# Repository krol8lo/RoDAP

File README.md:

# RoDAP
RoDAP - Robot Dzielnie Atakujący Przeciwników. Przykładowy projekt robota minisumo

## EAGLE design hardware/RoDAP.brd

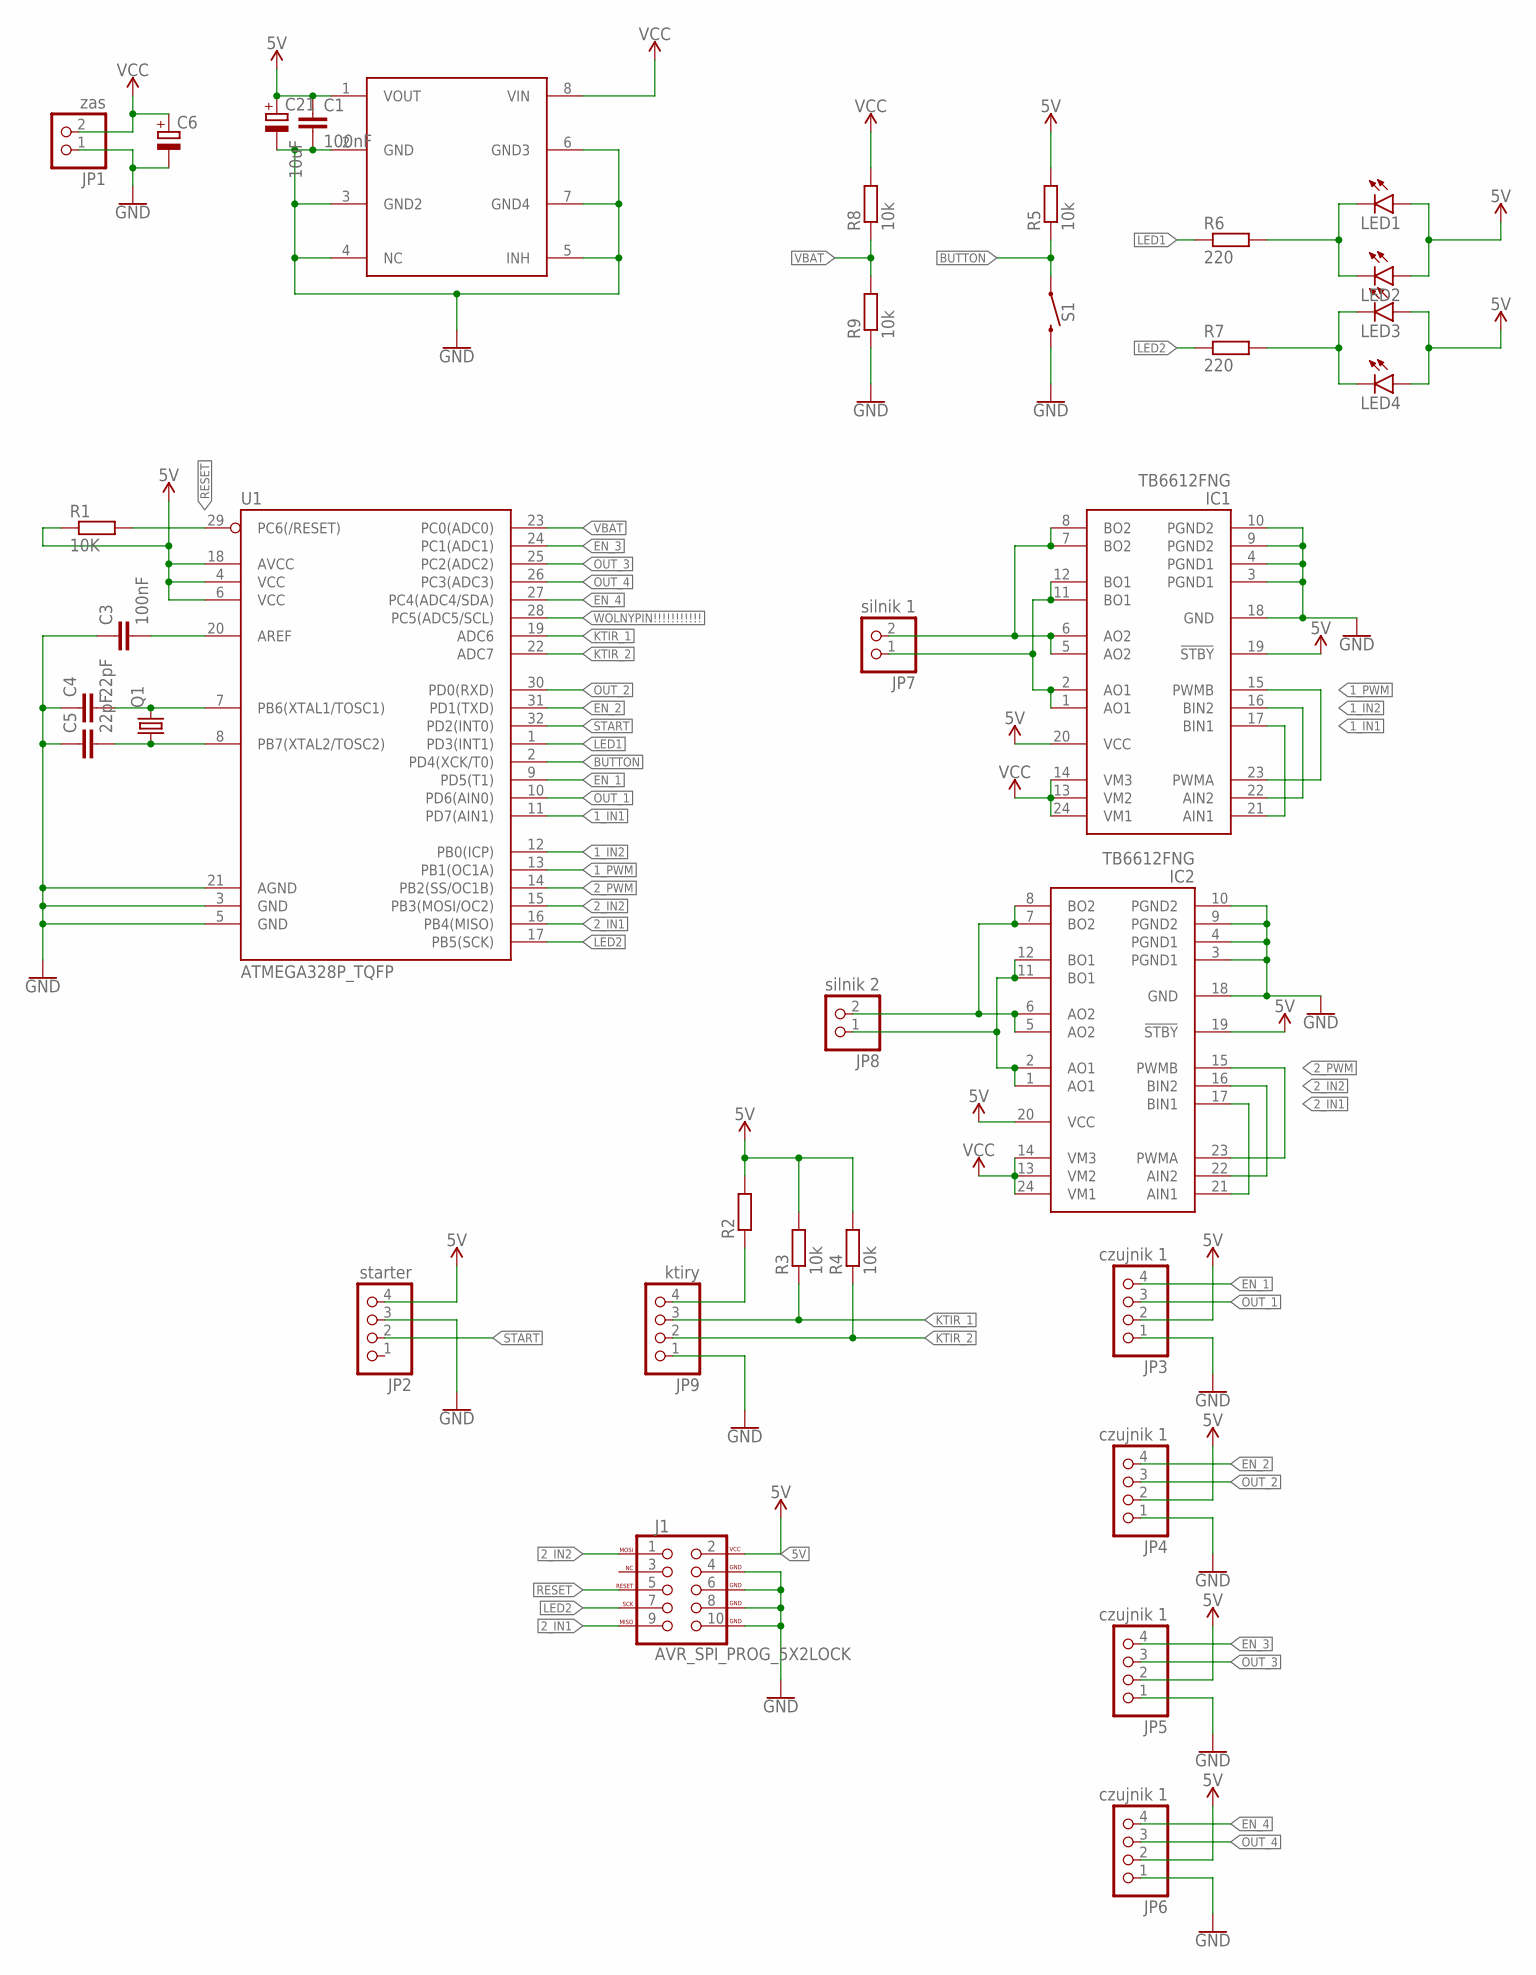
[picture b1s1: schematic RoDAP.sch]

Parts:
C1, C3: 100nF; C0805
C4, C5: 22pF; C0805
C6: CPOL-EUE2.5-7; E2,5-7
C21: 10uF; SMC_B
IC1, IC2: TB6612FNG; SSOP24
J1: AVR_SPI_PROG_5X2LOCK; 2X5-SHROUDED_LOCK
JP1: zas; 1X02
JP2: starter; 1X04
JP3, JP4, JP5, JP6: czujnik 1; 1X04
JP7: silnik 1; 1X02
JP8: silnik 2; 1X02
JP9: ktiry; 1X04
LED1, LED3: LED5MM
LED2, LED4: LEDSML0805; SML0805
Q1: CRYSTALHC49S; HC49/S
R1: 10K; R0805
R2: R-EU_R0805; R0805
R3, R4, R5, R8, R9: 10k; R0805
R6, R7: 220; R0805
S1: MOMENTARY-SWITCH-SPST-SMD-6.0X3.5MM; TACTILE_SWITCH_SMD_6.0X3.5MM
U1: ATMEGA328P_TQFP; TQFP32-08
U$4: KF50BD-TR; SOIC8-1.27-5X4MM

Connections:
1_IN1: IC1.17 (BIN1), IC1.21 (AIN1), U1.11 (PD7(AIN1))
1_IN2: IC1.16 (BIN2), IC1.22 (AIN2), U1.12 (PB0(ICP))
1_PWM: IC1.15 (PWMB), IC1.23 (PWMA), U1.13 (PB1(OC1A))
2_IN1: IC2.17 (BIN1), IC2.21 (AIN1), J1.9 (MISO), U1.16 (PB4(MISO))
2_IN2: IC2.16 (BIN2), IC2.22 (AIN2), J1.1 (MOSI), U1.15 (PB3(MOSI/OC2))
2_PWM: IC2.15 (PWMB), IC2.23 (PWMA), U1.14 (PB2(SS/OC1B))
5V: C1.1, C21.+, IC1.19 (!STBY), IC1.20 (VCC), IC2.19 (!STBY), IC2.20 (VCC), J1.2 (VCC), JP2.4, JP3.2, JP4.2, JP5.2, JP6.2, LED1.A, LED2.A, LED3.A, LED4.A, R1.1, R2.2, R3.2, R4.2, R5.2, U1.4 (VCC), U1.6 (VCC), U1.18 (AVCC), U$4.1 (VOUT)
BUTTON: R5.1, S1.1, U1.2 (PD4(XCK/T0))
EN_1: JP3.4, U1.9 (PD5(T1))
EN_2: JP4.4, U1.31 (PD1(TXD))
EN_3: JP5.4, U1.24 (PC1(ADC1))
EN_4: JP6.4, U1.27 (PC4(ADC4/SDA))
GND: C1.2, C3.1, C4.1, C5.1, C6.-, C21.-, IC1.3 (PGND1), IC1.4 (PGND1), IC1.9 (PGND2), IC1.10 (PGND2), IC1.18 (GND), IC2.3 (PGND1), IC2.4 (PGND1), IC2.9 (PGND2), IC2.10 (PGND2), IC2.18 (GND), J1.4 (GND), J1.6 (GND), J1.8 (GND), J1.10 (GND), JP1.1, JP2.3, JP3.1, JP4.1, JP5.1, JP6.1, JP9.1, R9.1, S1.2, U1.3 (GND), U1.5 (GND), U1.21 (AGND), U$4.2 (GND), U$4.3 (GND2), U$4.4 (NC), U$4.5 (INH), U$4.6 (GND3), U$4.7 (GND4)
KTIR_1: JP9.3, R3.1, U1.19 (ADC6)
KTIR_2: JP9.2, R4.1, U1.22 (ADC7)
LED1: R6.1, U1.1 (PD3(INT1))
LED2: J1.7 (SCK), R7.1, U1.17 (PB5(SCK))
unnamed: C3.2, U1.20 (AREF)
unnamed: IC2.5 (AO2), IC2.6 (AO2), IC2.7 (BO2), IC2.8 (BO2), JP8.2
unnamed: C4.2, Q1.2, U1.7 (PB6(XTAL1/TOSC1))
unnamed: C5.2, Q1.1, U1.8 (PB7(XTAL2/TOSC2))
unnamed: IC2.1 (AO1), IC2.2 (AO1), IC2.11 (BO1), IC2.12 (BO1), JP8.1
unnamed: JP9.4, R2.1
unnamed: LED1.K (C), LED2.C, R6.2
unnamed: LED3.K (C), LED4.C, R7.2
unnamed: IC1.5 (AO2), IC1.6 (AO2), IC1.7 (BO2), IC1.8 (BO2), JP7.2
unnamed: IC1.1 (AO1), IC1.2 (AO1), IC1.11 (BO1), IC1.12 (BO1), JP7.1
OUT_1: JP3.3, U1.10 (PD6(AIN0))
OUT_2: JP4.3, U1.30 (PD0(RXD))
OUT_3: JP5.3, U1.25 (PC2(ADC2))
OUT_4: JP6.3, U1.26 (PC3(ADC3))
RESET: J1.5 (RESET), R1.2, U1.29 (PC6(/RESET))
START: JP2.2, U1.32 (PD2(INT0))
VBAT: R8.1, R9.2, U1.23 (PC0(ADC0))
VCC: C6.+, IC1.13 (VM2), IC1.14 (VM3), IC1.24 (VM1), IC2.13 (VM2), IC2.14 (VM3), IC2.24 (VM1), JP1.2, R8.2, U$4.8 (VIN)
WOLNYPIN!!!!!!!!!!!: U1.28 (PC5(ADC5/SCL))

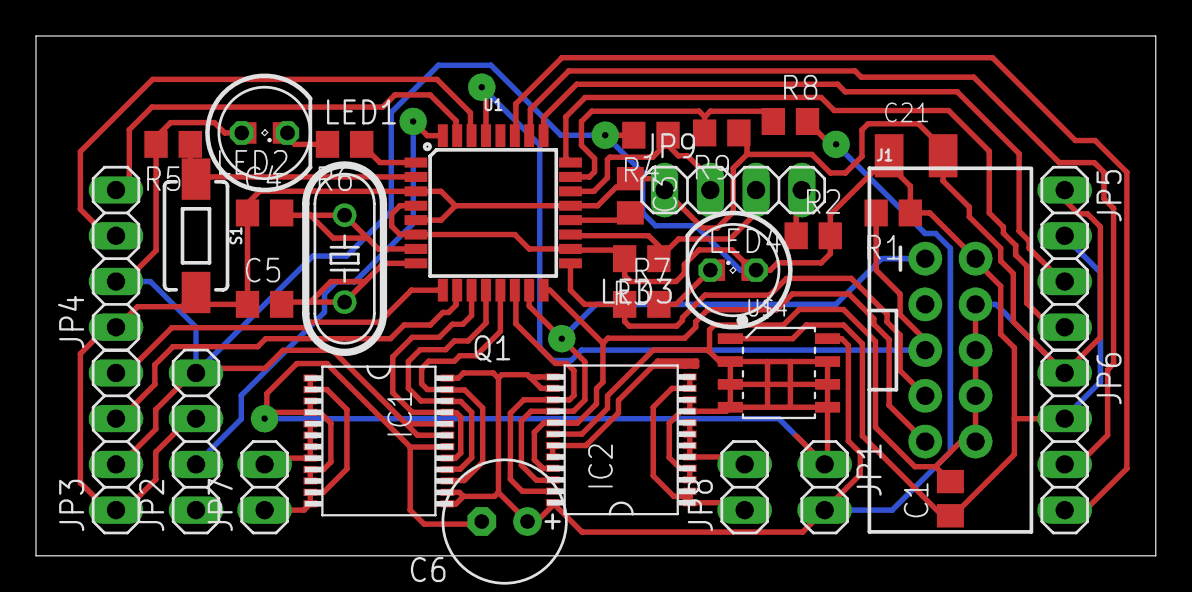
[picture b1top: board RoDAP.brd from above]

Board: 2 copper layers, 62.2 x 28.9 mm, 35 parts (0 on the bottom side), 35 nets.

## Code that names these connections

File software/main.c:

/*
main.c
Program robota minisumo o nazwie RoDAP
Projekt p³ytki i schemat dostêpne na githube:
github.com/krol8lo
Mikrokontroler to ATmega328

Uwaga!
Projekt jest udostêpniany jako pomoc naukowa.
Ca³oæ powstawa³a dwa tygodnie, w zwi¹zku z tym ani hardware ani software nie s¹ najpiêkniejsze.
Nie wszystkie rozwi¹zania s¹ m¹dre i warte powtórzenia - nale¿y czytaæ komentarze.
KRÓL 2019
*/

#include <avr/io.h>
#include <util/delay.h>
#include <avr/interrupt.h>

//Definicje rejestrów timerów - ³atwiejsze w u¿yciu
#define L_PWM OCR1AL
#define R_PWM OCR1BL

//Mo¿na te¿ zastosowaæ const
#define REVERSE_TIME 60
#define DEFAULT_PWM 200

//Struktura przechowuj¹ca dane z czujników przeciwnika - czytelnoæ kodu
volatile struct sensors_data
{
	uint8_t front[2];
	uint8_t rear[2];
	uint8_t front_last[2];
	uint8_t enemy;
} enemy;							//Niezbyt szczêliwie dobrana nazwa - enemy.enemy wygl¹da kiepsko

/*
Bardzo brzydka obs³uga startera z u¿yciem dwóch zmiennych
Zosta³a zrobiona w ten sposób ze wzglêdu na trudne do naprawy b³êdy w poprzednich próbach implementacji startera
*/
volatile uint8_t starta, startb;

uint8_t line[2];					//Stan czujników linii
uint8_t pit;						//Tryb serwisowy(pitstop)

//Zmenne steruj¹ce skrêcaniem i zawracaniem
volatile char turn;
volatile uint8_t turn_time;

void set_leds(uint8_t a, uint8_t b);
void enable_sensors(uint8_t a, uint8_t b, uint8_t c, uint8_t d);
void line_read();
void batt_read();
void go(int8_t dir_l, int8_t dir_r);	//Ustawia kierunek obrotu kó³(1 - przód, -1 - ty³, 0 - stop) - czytelnoæ kodu
void stop();							//Zatrzyanie

int main(void)
{
	DDRB = 0b00111111;
	DDRC = 0b00010010;
	DDRD = 0b10101010;
	
	EICRA = _BV(ISC00);
	EIMSK = _BV(INT0);
	
	TCCR1A = _BV(COM1A1) | _BV(COM1B1) |_BV(WGM10);
	TCCR1B = _BV(WGM12) | _BV(CS12);
	
	ADMUX = _BV(ADLAR) | _BV(REFS0) | _BV(MUX2) | _BV(MUX1);
	ADCSRA = _BV(ADEN);
	
	/*
	Nie by³o tego na zajêciach - pin change interrupt
	Pozwala na wyprowadzenie przerwania na prawie ka¿dym pinie GPIO,
	ale wymaga sprawdzenia, który pin wygenerowa³ przerwanie - patrz ni¿ej
	*/
	PCICR = _BV(PCIE2) | _BV(PCIE1);
	PCMSK2 = _BV(PCINT22) | _BV(PCINT16);
	PCMSK1 = _BV(PCINT10) | _BV(PCINT11);
	
	TCCR0A = _BV(WGM01);
	TCCR0B = _BV(CS02) | _BV(CS00);
	OCR0A = 255;
	
	starta = startb = 0;
	turn_time = 0;
	turn = 0;
	line[0] = line[1] = 0;
	enemy.front[0] = enemy.front[1] = 0;
	enemy.rear[0] = enemy.rear[1] = 0;
	enemy.front_last[0] = enemy.front_last[1] = 0;
	enemy.enemy = 0;
	pit = 0;
	
	//Mruganie ledami na pocz¹tku kodu pozwala znajdowaæ przypadkowe resety
	set_leds(1,0);
	_delay_ms(200);
	set_leds(0,1);
	_delay_ms(200);
	set_leds(0,0);
	
	batt_read();
	
	sei();
	
	while (1)
	{
		if(!starta && !startb)
		{
			if(PORTD & _BV(PD4))
			{
				pit = ~pit;
				if(pit)						//Tryb pitstopu - krêcenie ko³ami u³atwia czyszczenie kó³
				{
					go(1,1);
					L_PWM = R_PWM = DEFAULT_PWM;
				}
				else
				{
					stop();
				}
				_delay_ms(500);
			}
		}
		
		if(starta && startb)				//Po sygnale startera
		{
			set_leds(0,0);
			/*
			Ma³e oszustwo - kierunek obrotu na pocz¹tku wybierany jest prze³¹cznikiem.
			Pozwala to na szybsze znalenienie przeciwnika - krótszy obrót.
			Technika czêsto stosowana na zawodach czasem implementowana te¿ za pomoc¹ czujników -
			przed startem pokazujesz robotowi kierunek zas³aniaj¹c jeden z czujników.
			*/
			if(PINC & _BV(PC5))
			{
				go(1,-1);
			}
			else
			{
				go(-1,1);
			}
			turn = 'r';
			turn_time = REVERSE_TIME;		//Cofanie przez 60 cykli timera
			L_PWM = R_PWM = DEFAULT_PWM;
			enable_sensors(1,1,1,1);
			TIMSK0 = _BV(OCIE0A);
			startb = 0;
		}
		
		/*
		G³ówna logika robota
		Bardzo agresywne zatrzymywanie i zmiana kierunku obrotu kó³ ze wzglêdu na problemy z przyczepnoci¹ i s³abe silniki
		Z punktu widzenia estetyki kodu trochê za du¿o zagnie¿d¿onych if'ów
		*/
		if(starta && !startb)
		{
			if(enemy.enemy)
			{
				if(enemy.front[1] || enemy.front[0])
				{
					TIMSK0 = 0;
					turn = 0;
					turn_time = 0;
					if(enemy.front[1] && enemy.front[0])
					{
						go(1,1);
						L_PWM = R_PWM = 255;
						continue;
					}
					else if(enemy.front[1])
					{
						go(1,0);
						L_PWM = 255;
						turn = 'r';
						TIMSK0 = _BV(OCIE0A);
						turn_time = REVERSE_TIME*3;
					}
					else if(enemy.front[0])
					{
						go(0,1);
						R_PWM = 255;
						turn = 'r';
						TIMSK0 = _BV(OCIE0A);
						turn_time = REVERSE_TIME*3;
					}
					else
					{
						/*
						Taka sytuacja mo¿e mieæ miejsce po przerwaniu
						*/
						TIMSK0 = 0;
						turn = 0;
						turn_time = 0;
						go(1,1);
						L_PWM = R_PWM = DEFAULT_PWM;
					}
				}
				/*
				Tylko, gdy robot nie omija akurat krawêdzi
				Brak tego if'a powodowa³ b³êdy
				*/
				else if(turn == 0 || turn == 'r')
				{
					if(enemy.rear[1])
					{
						go(1,0);
						turn = 'r';
						TIMSK0 = _BV(OCIE0A);
						turn_time = REVERSE_TIME;
						L_PWM = DEFAULT_PWM;
					}
					if(enemy.rear[0])
					{
						go(0,1);
						turn = 'r';
						TIMSK0 = _BV(OCIE0A);
						turn_time = REVERSE_TIME;
						R_PWM = DEFAULT_PWM;
					}
				}
			}
			/*
			Gdy robot widzi przeciwnika ignoruje liniê
			*/
			line_read();
			if(line[0])
			{
				turn = 'p';
				TIMSK0 = _BV(OCIE0A);
				turn_time = REVERSE_TIME;
				go(-1,0);
				L_PWM = DEFAULT_PWM;
			}
			if(line[1])
			{
				turn = 'l';
				TIMSK0 = _BV(OCIE0A);
				turn_time = REVERSE_TIME;
				go(0,-1);
				R_PWM = DEFAULT_PWM;
			}
		}
		else
		{
			stop();
		}
	}
}

void set_leds(uint8_t a, uint8_t b)
{
	if(a)
	{
		PORTD &= ~_BV(PD3);
	}
	else
	{
		PORTD |= _BV(PD3);
	}
	if(b)
	{
		PORTB &= ~_BV(PB5);
	}
	else
	{
		PORTB |= _BV(PB5);
	}
}


void enable_sensors(uint8_t a, uint8_t b, uint8_t c, uint8_t d)
{
	if(a)
	{
		PORTD |= _BV(PD5);
	}
	else
	{
		PORTD &= ~_BV(PD5);
	}
	if(b)
	{
		PORTD |= _BV(PD1);
	}
	else
	{
		PORTD &= ~_BV(PD1);
	}
	if(c)
	{
		PORTC |= _BV(PC1);
	}
	else
	{
		PORTC &= ~_BV(PC1);
	}
	if(d)
	{
		PORTC |= _BV(PC4);
	}
	else
	{
		PORTC &= ~_BV(PC4);
	}
}

void line_read()	//Odczyt czujników linii
{
	//ADC6 - prawy
	//ADC7 - lewy
	ADMUX &= ~_BV(MUX0);	//ADC6
	ADCSRA |= _BV(ADSC);
	while(ADCSRA & _BV(ADSC));
	if(ADCH > 128)
	line[1] = 0;
	else
	line[1] = 1;
	
	ADMUX |= _BV(MUX0);	//ADC7
	ADCSRA |= _BV(ADSC);
	while(ADCSRA & _BV(ADSC));
	if(ADCH > 128)
	line[0] = 0;
	else
	line[0] = 1;
}

void go(int8_t dir_l, int8_t dir_r)		//Sterowanie mostkami
{
	if(dir_l == 1)
	{
		PORTD |= _BV(PD7);
		PORTB &= ~_BV(PB0);
	}
	else
	{
		if(dir_l == -1)
		{
			PORTB |= _BV(PB0);
			PORTD &= ~_BV(PD7);
		}
		else
		{
			if(dir_l == 0)
			{
				PORTB |= _BV(PB0);
				PORTD |= _BV(PD7);
			}
		}
	}
	if(dir_r == 1)
	{
		PORTB |= _BV(PB4);
		PORTB &= ~_BV(PB3);
	}
	else
	{
		if(dir_r == -1)
		{
			PORTB |= _BV(PB3);
			PORTB &= ~_BV(PB4);
		}
		else
		{
			if(dir_r == 0)
			{
				PORTB |= _BV(PB3);
				PORTB |= _BV(PB4);
			}
		}
	}
}

void stop()
{
	OCR1AL = 0;
	OCR1BL = 0;
	enable_sensors(0,0,0,0);
	go(0,0);
}

void batt_read()		//Pomiar stanu akumulatora
{
	ADMUX = _BV(ADLAR) | _BV(REFS0);
	ADCSRA |= _BV(ADSC);
	while(ADCSRA & _BV(ADSC));
	if(ADCH < 191)
	{
		for(uint8_t i = 0; i < 10; i++)		//Sygnalizacja niskiego napiêcia
		{
			set_leds(1,0);
			_delay_ms(50);
			set_leds(0,0);
			_delay_ms(50);
		}
	}
	/*
	Przywrócenie rejestru do stanu pocz¹tkowego dla funkcji line_read()
	Niezbyt eleganckie rozwi¹zanie, ale za to szybsze - batt_read() wywo³ywane jest tylko po resecie
	*/
	ADMUX = _BV(ADLAR) | _BV(REFS0) | _BV(MUX2) | _BV(MUX1);
}

/*
Obs³uga przerwañ pin change
Wype³nianie struktury enemy danymi z czujników w zale¿noci od stanów pinów podczas przewania
*/
ISR(PCINT1_vect)
{
	enemy.front_last[1] = enemy.front[1];
	enemy.rear[1] = !((PINC & _BV(PC2)) >> PC2);
	enemy.front[1] = !((PINC & _BV(PC3)) >> PC3);
	enemy.enemy |= !(enemy.front[1] | enemy.rear[1] | enemy.front[0] | enemy.rear[0]);
}

ISR(PCINT2_vect)
{
	enemy.front_last[0] = enemy.front[0];
	enemy.rear[0] = !((PIND & _BV(PD0)) >> PD0);
	enemy.front[0] = !((PIND & _BV(PD6)) >> PD6);
	enemy.enemy |= !(enemy.front[0] | enemy.rear[0] | enemy.front[1] | enemy.rear[1]);
}

ISR(TIMER0_COMPA_vect)	//Przerwanie timera s³u¿¹ce do skrêcania i zawracania przez okrelony czas (zmienna turn_time)
{
	if(turn_time-- == 0)
	{
		TIMSK0 = 0;
		turn = 0;
		go(1,1);
		L_PWM = R_PWM = DEFAULT_PWM;
	}
}


ISR(INT0_vect)			//Starter
{
	if(PIND & _BV(PD2))
	{
		starta = startb = 1;
	}
	else
	{
		stop();
		starta = 0;
	}
}

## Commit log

2019-07-30 Dodano kod robota
2019-08-18 Dodano folder hardware
2020-02-10 Zmiany w procedurze startowej i algorytmie

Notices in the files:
parts and their libraries:
SparkFun-IC-Microcontroller: Licensing: Creative Commons ShareAlike 4.0 International - https://creativecommons.org/licenses/by-sa/4.0
